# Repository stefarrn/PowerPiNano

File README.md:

# PowerPiNano
The PowerPiNano is a development Board based on the RP2040 microcontroller, except it's highly customizable with pull-up/down resistor networks, "high" current capable GPIOs and flash memory up to 16MB.

## The very first revision (fully functional though with visual design errors, fixed for V1.1):

## Pin Description:

#### General purpose IO pins (GPIO):
All pins marked with the Öetter "G" are general purpose IO-pins, with the number correspind to the GPIO pin number of the IC

#### Optional pull-up/down resistors:
G0 to G3 and G4 to G7 each have a footprint for pull-up/down resistor networks respectivley, which can be populated or left unpopulated by personal preference

#### "High" current output pins:
All Pins marked with an "O" are "high" current output only pins, which also have an LED attached for easy debugging without needing to probe the pins. They are directly connected to the collector of MMBT3904 NPN transistors. They therefore switch to GND when the corresponding GPIO number is toggled HIGH by the IC, switching the corresponding GPIO LOW or floating will result in the output Pin being pulled HIGH through the LED. The output pins are suitable for switching up to 40V at 200mA (recommended 30V at 100mA).

#### Analog input pins:
Pins A26 to A29 are the four inputs to the analog to digital converter (ADC) of the RP2040. The reference voltage of the RP2040 is directly ried to 3V3.

#### Power pins:
The pins marked 3V3 and GND are exactly what you'd expect. The board can be externally powered (only 3,3V!) through one of the 3V3 pins, as long as it is not simoutanously being powered through USB or the V_EXT pin.

#### V_EXT pin:
The V_EXT pin is directly connected to the input of the onboard 3,3V regulator and is intended for powering the board from an external powersource. CAUTION: V_EXT is directly connected to the 5V pin of the USB connector, NEVER power the board through V_EXT if any USB device is connected. if the board is powered through USB V_EXT can be used as a 5V output pin.

## Setup
When the Board is being flashed for the first time after assembly, the BOOT Button needs to be held down while plugging it in in order to put the RP2040 in boot mode. It should then show up as a USB storage device, and flashing any code onto it will also flash the bootloader, such that it will not need to be put into boot mode for future programming.

It is also highly recommended to check all voltage rails aswell as the USB datalines for shorts before plugging a freshly assembled Board in for the first time.

## Troubleshooting
If the Board does not show up as a USB storage device after plugging it in while holding down the boot button
1. unplug it and try again
2. make sure all voltage rails are present, including the 1,1V core voltage
3. check for solder bridges between the data pins of the USB connector
4. try plugging the board into a device running linux, windows sometimes refuses to detect the devices as USB storage

#### Sources used:
- The amazing documentation for the RP2040 microcontroller: https://datasheets.raspberrypi.com/rp2040/hardware-design-with-rp2040.pdf
- 3D-Model for the SMD Button: https://grabcad.com/library/tactile-switches-6mm-smt-1
- 3D-Model for the mini USB connector: https://grabcad.com/library/two-type-of-mini-usb-receptacle-type-b-5-pin-1

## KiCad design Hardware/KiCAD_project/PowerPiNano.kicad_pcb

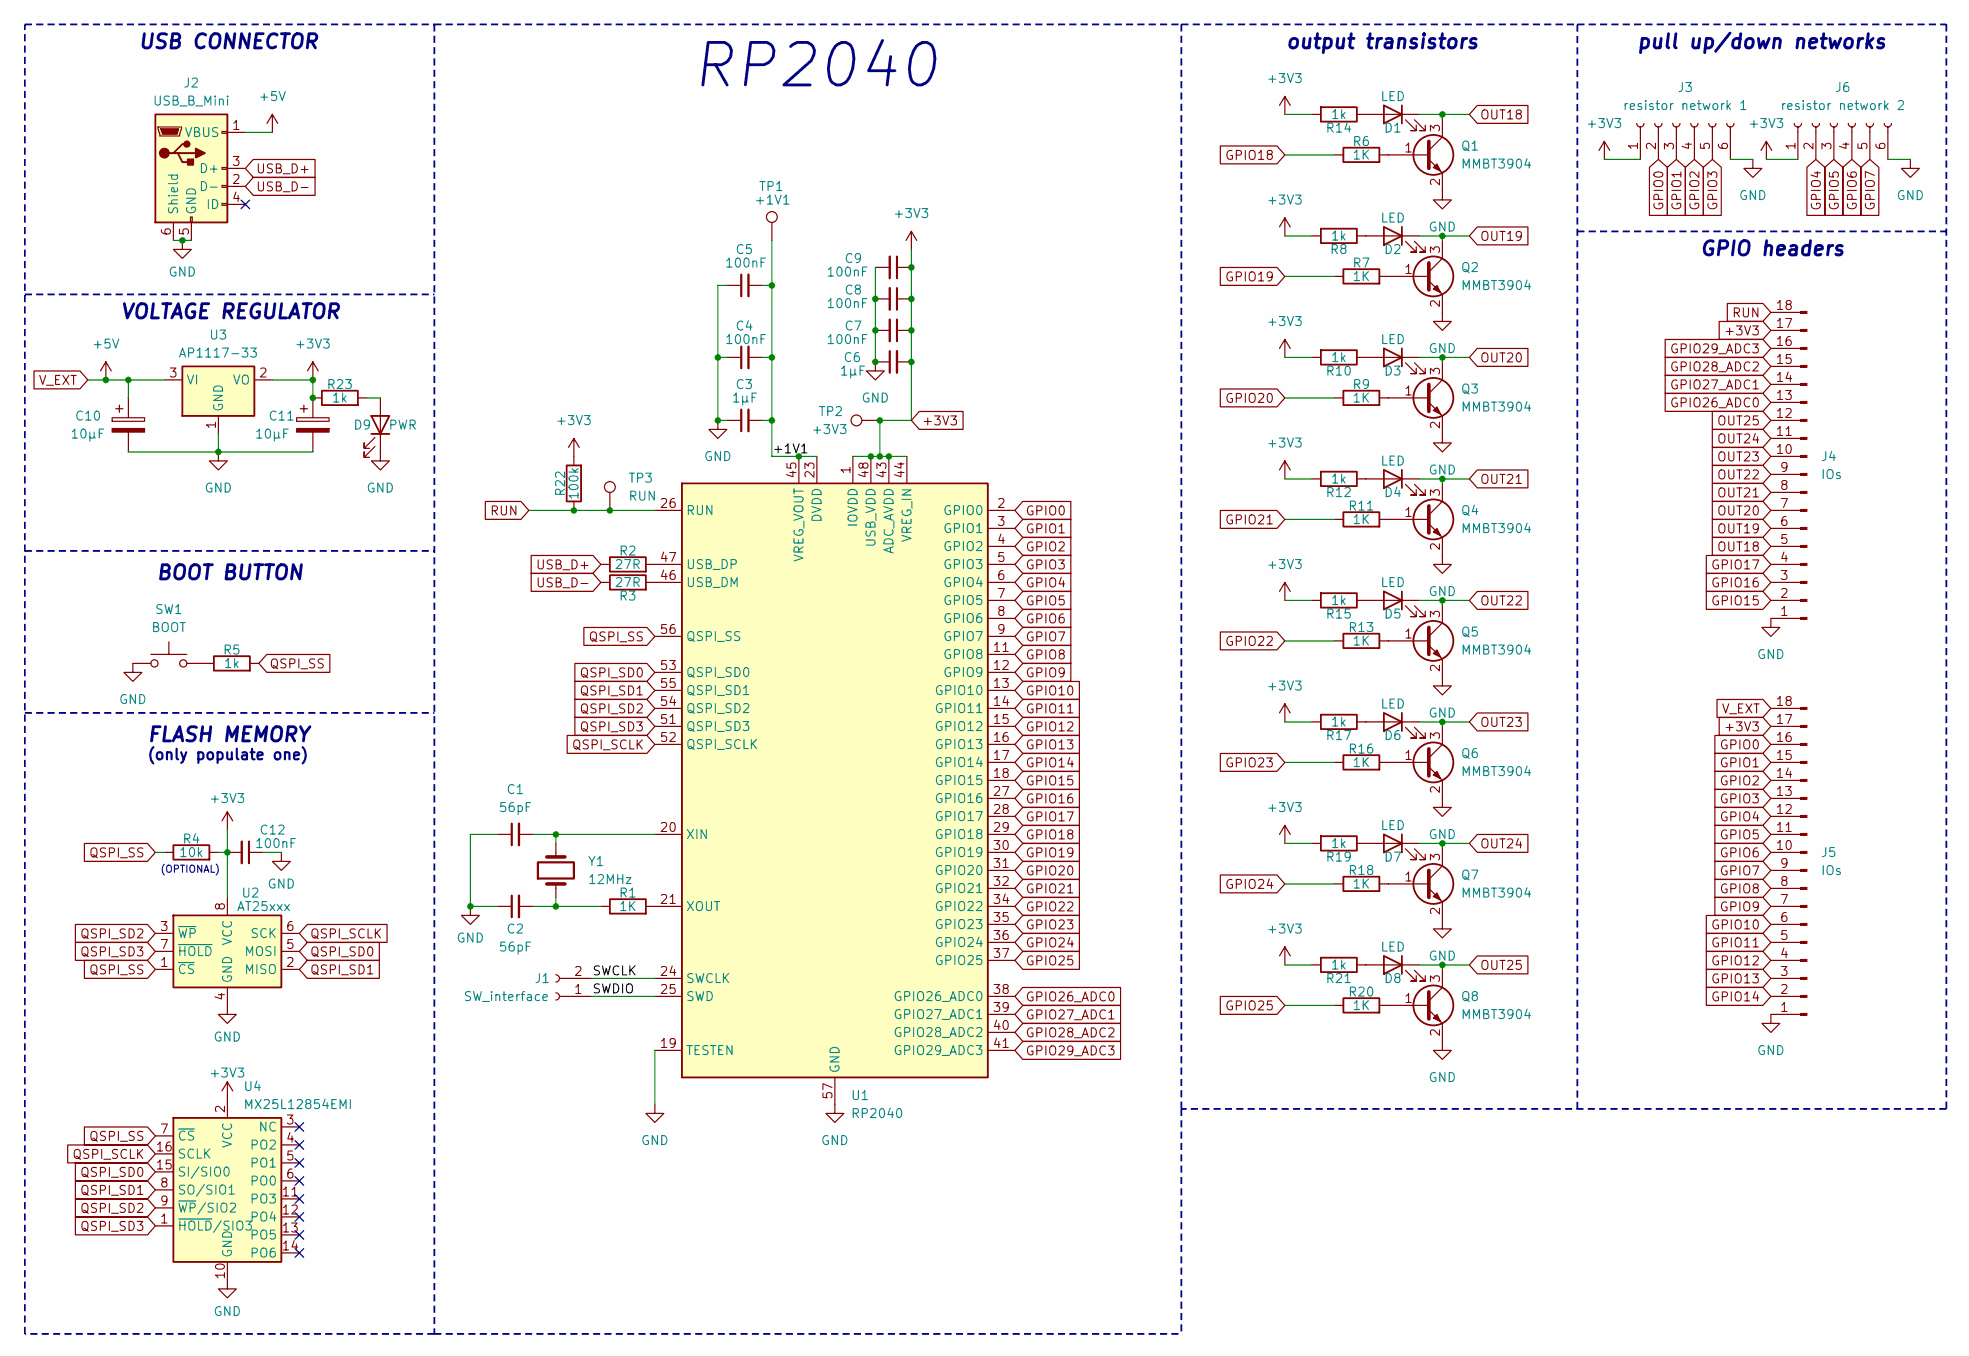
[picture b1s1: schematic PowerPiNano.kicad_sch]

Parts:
C1, C2: 56pF; C_0805_2012Metric
C3, C6: 1µF; C_0805_2012Metric
C4, C5, C7, C8, C9, C12: 100nF; C_0805_2012Metric
C10, C11: 10µF; CP_Elec_4x3
D1, D2, D3, D4, D5, D6, D7, D8: LED; LED_0603_1608Metric
D9: PWR; LED_0603_1608Metric
J1: SW_interface; PinHeader_1x02_P2.54mm_Vertical
J2: USB_B_Mini; Mini_USB
J3: resistor network 1; PinSocket_1x06_P2.54mm_Vertical
J4, J5: IOs; PinHeader_1x18_P2.54mm_Vertical
J6: resistor network 2; PinSocket_1x06_P2.54mm_Vertical
Q1, Q2, Q3, Q4, Q5, Q6, Q7, Q8: MMBT3904; SOT-23
R1, R6, R7, R9, R11, R13, R16, R18, R20: 1K; R_MiniMELF_MMA-0204
R2, R3: 27R; R_MiniMELF_MMA-0204
R4: 10k; R_MiniMELF_MMA-0204
R5, R8, R10, R12, R14, R15, R17, R19, R21, R23: 1k; R_MiniMELF_MMA-0204
R22: 100k; R_MiniMELF_MMA-0204
SW1: BOOT; 6x6mm_smd_tactile_button
TP1: +1V1; TestPoint_Pad_D1.0mm
TP2: +3V3; TestPoint_Pad_D1.0mm
TP3: RUN; TestPoint_Pad_D1.0mm
U1: RP2040; QFN-56-1EP_7x7mm_P0.4mm_EP3.2x3.2mm
U2: AT25xxx; SOIC-8W_5.3x5.3mm_P1.27mm
U3: AP1117-33; SOT-223-3_TabPin2
U4: MX25L12854EMI; SOIC-16W_7.5x10.3mm_P1.27mm
Y1: 12MHz; Crystal_HC49-4H_Vertical

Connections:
+3V3: C6.2, C7.1, C8.1, C9.1, C11.1, C12.2, J3.1, J4.17, J5.17, J6.1, R4.2, R8.2, R10.2, R12.2, R14.2, R15.2, R17.2, R19.2, R21.2, R22.2, R23.1, TP2.1, U1.1 (IOVDD), U1.10 (IOVDD), U1.22 (IOVDD), U1.33 (IOVDD), U1.42 (IOVDD), U1.43 (ADC_AVDD), U1.44 (VREG_IN), U1.48 (USB_VDD), U1.49 (IOVDD), U2.8 (VCC), U3.2 (VO), U4.2 (VCC)
/+1V1: C3.2, C4.2, C5.2, TP1.1, U1.23 (DVDD), U1.45 (VREG_VOUT), U1.50 (DVDD)
/SWCLK: J1.2, U1.24 (SWCLK)
/SWDIO: J1.1, U1.25 (SWD)
GND: C1.1, C2.1, C3.1, C4.1, C5.1, C6.1, C7.2, C8.2, C9.2, C10.2, C11.2, C12.1, D9.1 (K), J2.5 (GND), J2.6 (Shield), J3.6, J4.1, J5.1, J6.6, Q1.2 (E), Q2.2 (E), Q3.2 (E), Q4.2 (E), Q5.2 (E), Q6.2 (E), Q7.2 (E), Q8.2 (E), SW1.1, U1.19 (TESTEN), U1.57 (GND), U2.4 (GND), U3.1 (GND), U4.10 (GND)
GPIO0: J3.2, J5.16, U1.2 (GPIO0)
GPIO1: J3.3, J5.15, U1.3 (GPIO1)
GPIO2: J3.4, J5.14, U1.4 (GPIO2)
GPIO3: J3.5, J5.13, U1.5 (GPIO3)
GPIO4: J5.12, J6.2, U1.6 (GPIO4)
GPIO5: J5.11, J6.3, U1.7 (GPIO5)
GPIO6: J5.10, J6.4, U1.8 (GPIO6)
GPIO7: J5.9, J6.5, U1.9 (GPIO7)
GPIO8: J5.8, U1.11 (GPIO8)
GPIO9: J5.7, U1.12 (GPIO9)
GPIO10: J5.6, U1.13 (GPIO10)
GPIO11: J5.5, U1.14 (GPIO11)
GPIO12: J5.4, U1.15 (GPIO12)
GPIO13: J5.3, U1.16 (GPIO13)
GPIO14: J5.2, U1.17 (GPIO14)
GPIO15: J4.2, U1.18 (GPIO15)
GPIO16: J4.3, U1.27 (GPIO16)
GPIO17: J4.4, U1.28 (GPIO17)
GPIO18: R6.1, U1.29 (GPIO18)
GPIO19: R7.1, U1.30 (GPIO19)
GPIO20: R9.1, U1.31 (GPIO20)
GPIO21: R11.1, U1.32 (GPIO21)
GPIO22: R13.1, U1.34 (GPIO22)
GPIO23: R16.1, U1.35 (GPIO23)
GPIO24: R18.1, U1.36 (GPIO24)
GPIO25: R20.1, U1.37 (GPIO25)
GPIO26_ADC0: J4.13, U1.38 (GPIO26_ADC0)
GPIO27_ADC1: J4.14, U1.39 (GPIO27_ADC1)
GPIO28_ADC2: J4.15, U1.40 (GPIO28_ADC2)
GPIO29_ADC3: J4.16, U1.41 (GPIO29_ADC3)
unnamed: C2.2, R1.1, Y1.1
unnamed: D1.2 (A), R14.1
unnamed: D2.2 (A), R8.1
unnamed: D3.2 (A), R10.1
unnamed: D4.2 (A), R12.1
unnamed: D5.2 (A), R15.1
unnamed: D6.2 (A), R17.1
unnamed: D7.2 (A), R19.1
unnamed: D8.2 (A), R21.1
unnamed: D9.2 (A), R23.2
unnamed: Q1.1 (B), R6.2
unnamed: Q2.1 (B), R7.2
unnamed: Q3.1 (B), R9.2
unnamed: Q4.1 (B), R11.2
unnamed: Q5.1 (B), R13.2
unnamed: Q6.1 (B), R16.2
unnamed: Q7.1 (B), R18.2
unnamed: Q8.1 (B), R20.2
unnamed: R5.1, SW1.2
unnamed: R3.2, U1.46 (USB_DM)
unnamed: R2.2, U1.47 (USB_DP)
unnamed: C1.2, U1.20 (XIN), Y1.2
unnamed: R1.2, U1.21 (XOUT)
OUT18: D1.1 (K), J4.5, Q1.3 (C)
OUT19: D2.1 (K), J4.6, Q2.3 (C)
OUT20: D3.1 (K), J4.7, Q3.3 (C)
OUT21: D4.1 (K), J4.8, Q4.3 (C)
OUT22: D5.1 (K), J4.9, Q5.3 (C)
OUT23: D6.1 (K), J4.10, Q6.3 (C)
OUT24: D7.1 (K), J4.11, Q7.3 (C)
OUT25: D8.1 (K), J4.12, Q8.3 (C)
QSPI_SCLK: U1.52 (QSPI_SCLK), U2.6 (SCK), U4.16 (SCLK)
QSPI_SD0: U1.53 (QSPI_SD0), U2.5 (MOSI), U4.15 (SI/SIO0)
QSPI_SD1: U1.55 (QSPI_SD1), U2.2 (MISO), U4.8 (SO/SIO1)
QSPI_SD2: U1.54 (QSPI_SD2), U2.3 (~WP), U4.9 (~WP/SIO2)
QSPI_SD3: U1.51 (QSPI_SD3), U2.7 (~HOLD), U4.1 (~HOLD/SIO3)
QSPI_SS: R4.1, R5.2, U1.56 (QSPI_SS), U2.1 (~CS), U4.7 (~CS)
RUN: J4.18, R22.1, TP3.1, U1.26 (RUN)
USB_D+: J2.3 (D+), R2.1
USB_D-: J2.2 (D-), R3.1
V_EXT: C10.1, J2.1 (VBUS), J5.18, U3.3 (VI)

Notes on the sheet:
(only populate one)
pull up/down networks
RP2040
GPIO headers
USB CONNECTOR
output transistors
(OPTIONAL)
BOOT BUTTON
VOLTAGE REGULATOR
FLASH MEMORY

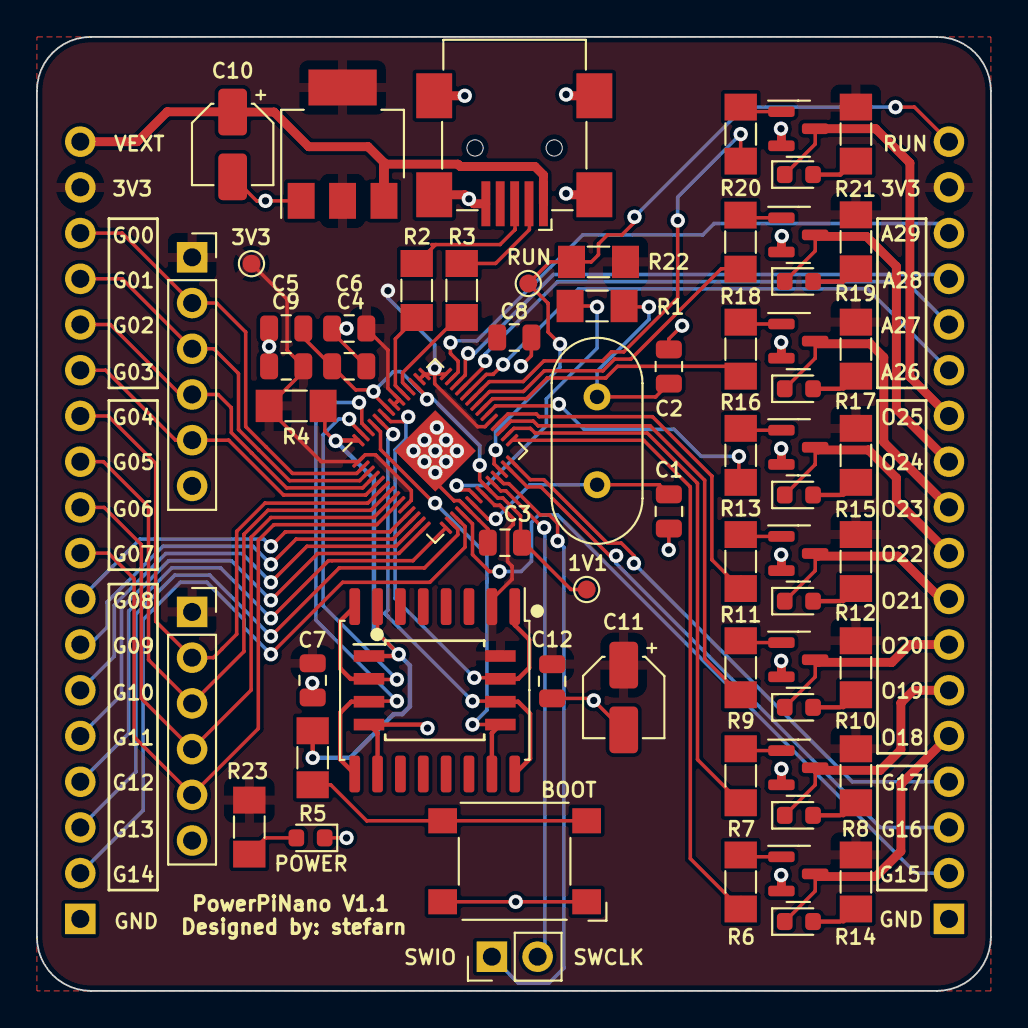
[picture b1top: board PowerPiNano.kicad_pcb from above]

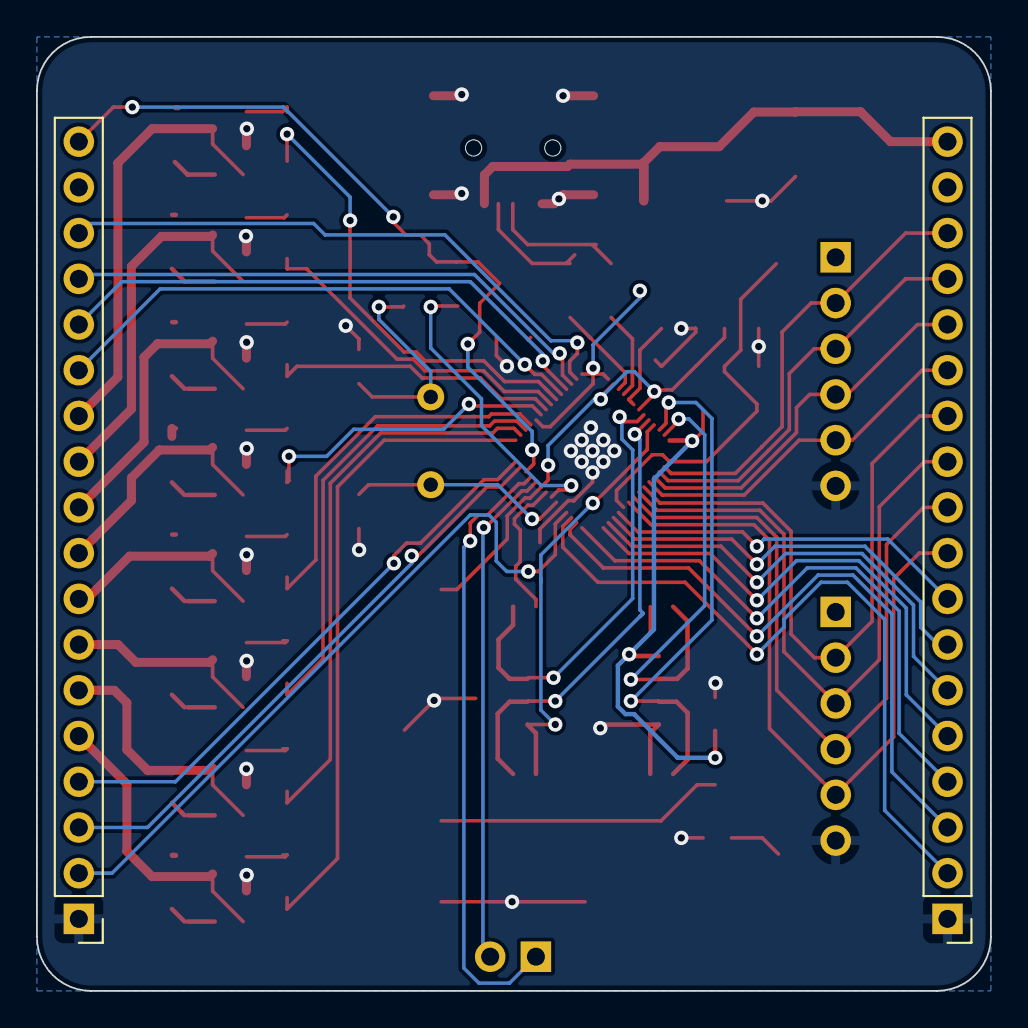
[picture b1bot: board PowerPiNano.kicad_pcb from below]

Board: 2 copper layers, 53.0 x 53.0 mm, 67 parts (2 on the bottom side), 76 nets.

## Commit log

2024-03-19 KiCAD files design files added
2024-03-19 updated KiCAD files
2024-03-20 README.md aktualisieren
2024-03-22 created gerber files and tidied up files system
2024-03-24 replaced schematic symbols of the electrolytic caps for the correct ones
